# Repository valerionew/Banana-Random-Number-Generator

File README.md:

# Banana Random Number Generator

## Project description 
An Arduino based true random number generator. Takes it's peculiar name from the potassium-40 present in bananas, used as radiation source for the random number generatation.  
  
_Disclaimer: the radioactivity from the bananas doesn't quite make the difference, the background radiation is more than enough to make the generator work. Potassium is definitely detected, some tests conducted with pure KCl and KOH showed a huge increase in the detector activity._

1. [Project status](#project-status)  
1. [Hardware](#hardware)  
1. [Software](#software) 
1. [Enclosure](#enclosure) 

## Project status 
The current release is fully working. 
## Hardware 
The hardware is based around the popular ATMega328P and the STS-5 (a.k.a. CTC-5) Geiger-Müller tube.
## Software

As of this moment there are available two versions of the firmware:
- **minimal_test.c**: this version is fully compatible with the unmodified hardware. It uses the hardware interrupt INT0 and has proven to be unreliable when brought into an arduino environment due to interferences with the millis() function from the Wiring core. On it's own works with no problems. [Read more on this, in italian](https://www.valerionappi.it/chi-quadro/)
- **minimal_test_with capture.c**: this version and has proven to be much more reliable than the previous, since it captures the timer stamp via dedicated hardware and it's not subject to software delays. It's based on the timer capture function on PB0/ICP1 pin of the ATMega. This version needs a bodge wire between pin PD2 and pin PB0, as shown below:  

I'm currently working on an arduino version on the software, that will be published in this repo as soon as it gives consistent results.
In the future another version of the firmware which makes use of the hardware as a plain Geiger counter might be developed. Any help is welcome!
## Enclosure
The board is designed to fit in a laser cut acrylic enclosure to protect the user from the high voltage present onboard. 
The enclosure design files are included and licensed under [CC-BY-SA 4.0 license](http://creativecommons.org/licenses/by-sa/4.0/)

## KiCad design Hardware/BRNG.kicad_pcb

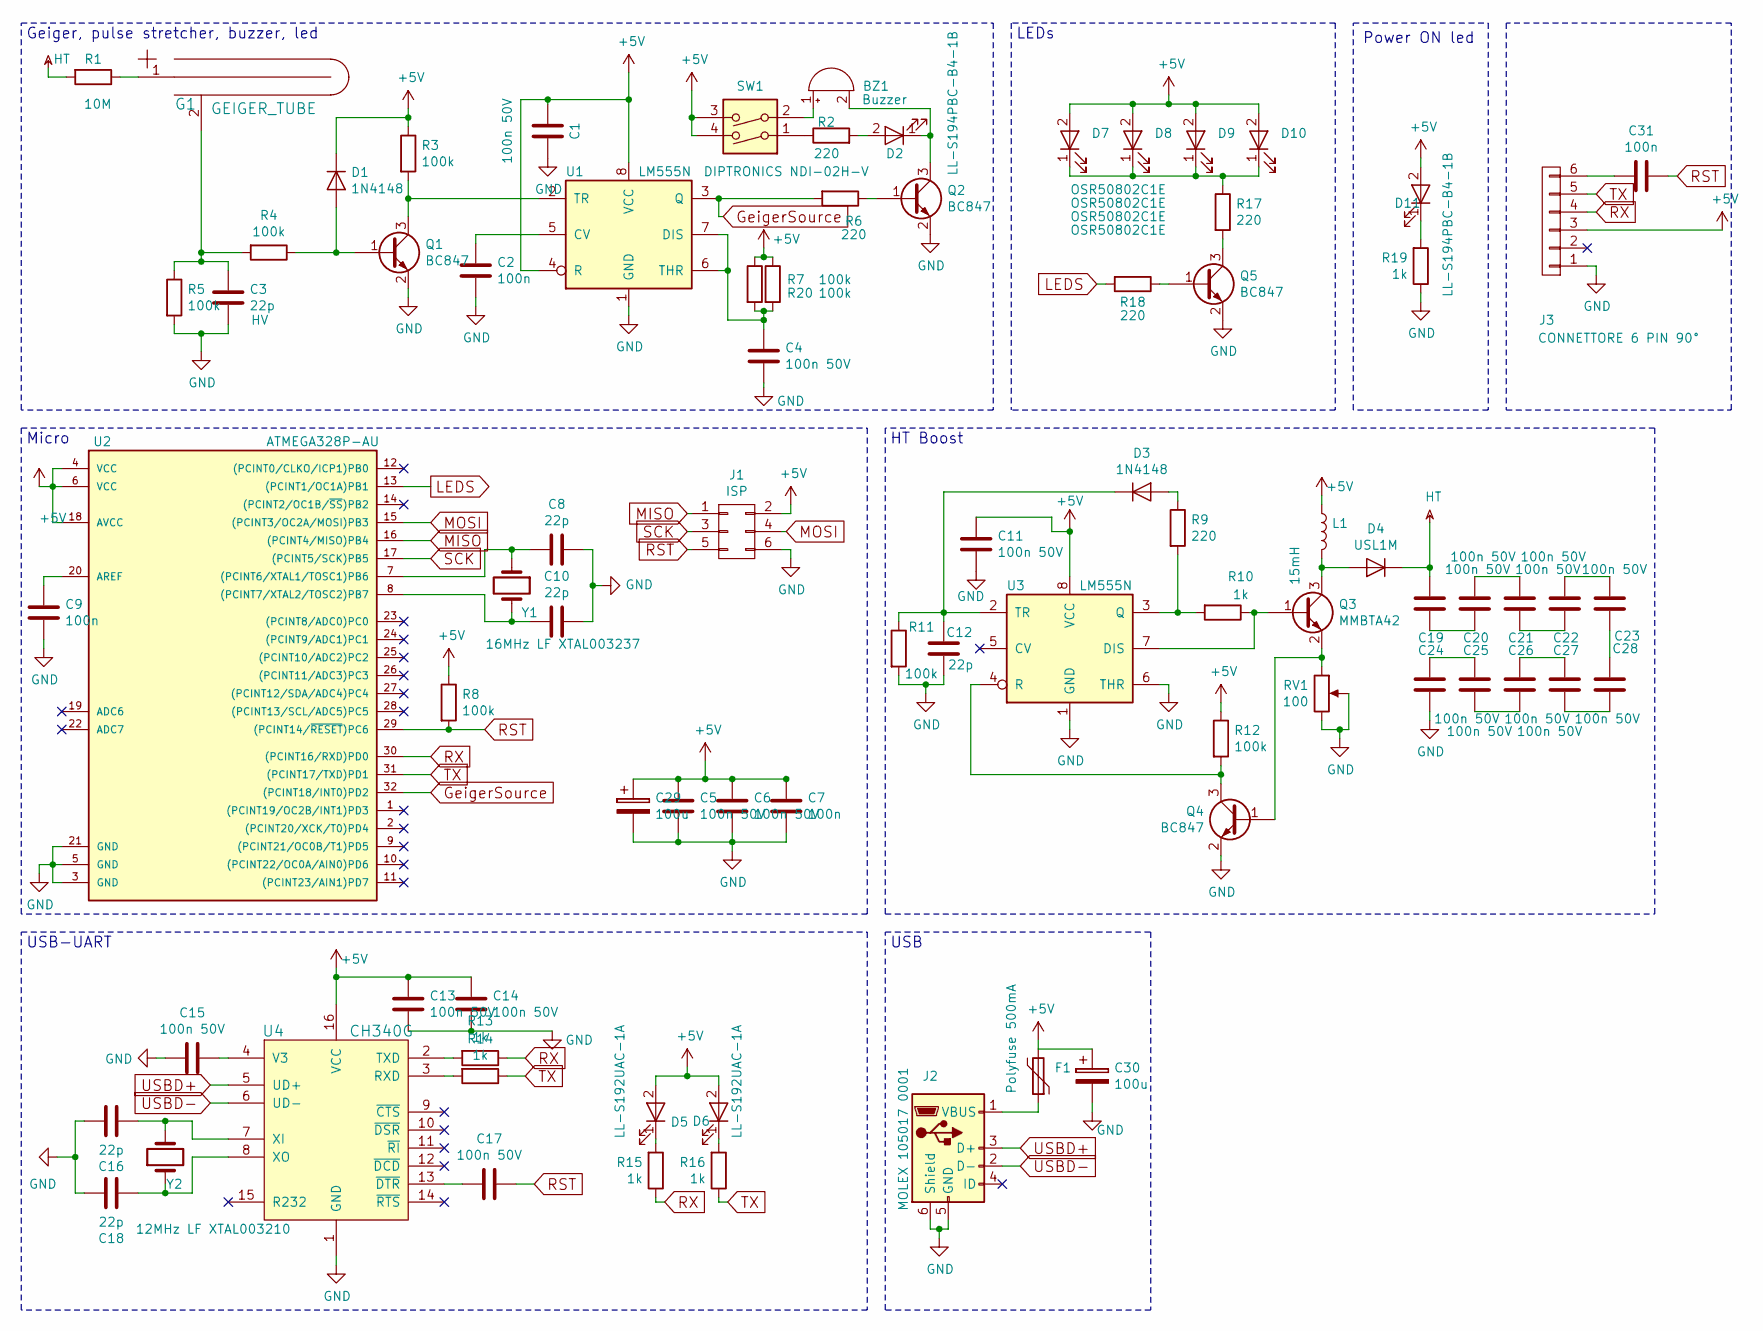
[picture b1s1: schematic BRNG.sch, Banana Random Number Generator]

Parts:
BZ1: Buzzer; Buzzer_12x9.5RM7.6
C1, C4, C5, C6, C11, C13, C14, C15, C17, C19, C20, C21, C22, C23, C24, C25, C26, C27, C28: 100n 50V; C_0805_HandSoldering
C2, C7, C9, C31: 100n; C_0805_HandSoldering
C3, C8, C10, C12, C16, C18: 22p; C_0805_HandSoldering
C29, C30: 100u; CP_Elec_6.3x5.3
D1, D3: 1N4148; D_SOD-123
D2, D11: LL-S194PBC-B4-1B; LED_0603_HandSoldering
D4: USL1M; D_SOD-123
D5, D6: LL-S192UAC-1A; LED_0603_HandSoldering
D7, D8, D9, D10: OSR50802C1E; 0802_side_led
F1: Polyfuse 500mA; R_1210_HandSoldering
G1: GEIGER_TUBE; Geiger
J1: ISP; Pin_Header_Straight_2x03_Pitch2.54mm
J2: MOLEX 105017 0001; USB_Micro-B_Molex-105017-0001
J3: CONNETTORE 6 PIN 90°; Pin_Header_Angled_1x06_Pitch2.54mm
L1: 15mH; L_Radial_D7.2mm_P3.00mm_MuRATA_1700
Q1, Q2, Q4, Q5: BC847; SOT-23_Handsoldering
Q3: MMBTA42; SOT-23_Handsoldering
R1: 10M; R_1206_HandSoldering
R2, R6, R9, R17, R18: 220; R_0805_HandSoldering
R3, R4, R5, R7, R8, R11, R12, R20: 100k; R_0805_HandSoldering
R10, R13, R14, R15, R16, R19: 1k; R_0805_HandSoldering
RV1: 100; Potentiometer_Trimmer_Vishay_T73XW_Vertical
SW1: DIPTRONICS NDI-02H-V; SW_DIP_x2_W7.62mm_Slide
U1, U3: LM555N; SOIC-8_3.9x4.9mm_Pitch1.27mm
U2: ATMEGA328P-AU; TQFP-32_7x7mm_Pitch0.8mm
U4: CH340G; SOP-16_4.4x10.4mm_Pitch1.27mm
Y1: 16MHz LF XTAL003237; Crystal_SMD_HC49-SD_HandSoldering
Y2: 12MHz LF XTAL003210; Crystal_SMD_HC49-SD_HandSoldering

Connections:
+5V: C1.2, C5.1, C6.1, C7.1, C11.1, C13.1, C14.1, C29.1, C30.1, D1.1 (K), D5.2 (A), D6.2 (A), D7.2 (A), D8.2 (A), D9.2 (A), D10.2 (A), D11.2 (A), F1.2, J1.2, J3.3, L1.1, R3.1, R7.1, R8.1, R12.1, R20.1, SW1.3, SW1.4, U1.4 (R), U1.8 (VCC), U2.4 (VCC), U2.6 (VCC), U2.18 (AVCC), U3.8 (VCC), U4.16 (VCC); also elsewhere on the board
GND: C1.1, C2.2, C3.2, C4.2, C5.2, C6.2, C7.2, C8.1, C9.2, C10.1, C11.2, C12.2, C13.2, C14.2, C15.2, C16.1, C18.1, C24.2, C29.2, C30.2, J1.6, J2.5 (GND), J2.6 (Shield), J3.1, Q1.2 (E), Q2.2 (E), Q4.2 (E), Q5.2 (E), R5.2, R11.2, R19.1, RV1.2, RV1.3, U1.1 (GND), U2.3 (GND), U2.5 (GND), U2.21 (GND), U3.1 (GND), U3.6 (THR), U4.1 (GND); also elsewhere on the board
GeigerSource: R6.2, U1.3 (Q), U2.32 ((PCINT18/INT0)PD2)
HT: C19.1, D4.1 (K), R1.2
LEDS: R18.2, U2.13 ((PCINT1/OC1A)PB1)
MISO: J1.1, U2.16 ((PCINT4/MISO)PB4); also elsewhere on the board
MOSI: J1.4, U2.15 ((PCINT3/OC2A/MOSI)PB3); also elsewhere on the board
unnamed: BZ1.1 (-), SW1.2
unnamed: BZ1.2 (+), D2.1 (K), Q2.3 (C)
unnamed: C2.1, U1.5 (CV)
unnamed: C3.1, G1.2, R4.2, R5.1
unnamed: C4.1, R7.2, R20.2, U1.6 (THR), U1.7 (DIS)
unnamed: C8.2, U2.7 ((PCINT6/XTAL1/TOSC1)PB6), Y1.1
unnamed: C9.1, U2.20 (AREF)
unnamed: C10.2, U2.8 ((PCINT7/XTAL2/TOSC2)PB7), Y1.2
unnamed: C12.1, D3.1 (K), R11.1, U3.2 (TR)
unnamed: C15.1, U4.4 (V3)
unnamed: C16.2, U4.7 (XI), Y2.2
unnamed: C17.2, U4.13 (~DTR)
unnamed: C18.2, U4.8 (XO), Y2.1
unnamed: C19.2, C20.2
unnamed: C20.1, C21.1
unnamed: C21.2, C22.2
unnamed: C22.1, C23.1
unnamed: C23.2, C28.1
unnamed: C24.1, C25.1
unnamed: C25.2, C26.2
unnamed: C26.1, C27.1
unnamed: C27.2, C28.2
unnamed: C31.1, J3.6
unnamed: D1.2 (A), Q1.1 (B), R4.1
unnamed: D2.2 (A), R2.2
unnamed: D3.2 (A), R9.1
unnamed: D4.2 (A), L1.2, Q3.3 (C)
unnamed: D5.1 (K), R15.2
unnamed: D6.1 (K), R16.2
unnamed: D7.1 (K), D8.1 (K), D9.1 (K), D10.1 (K), R17.1
unnamed: D11.1 (K), R19.2
unnamed: F1.1, J2.1 (VBUS)
unnamed: G1.1, R1.1
unnamed: Q1.3 (C), R3.2, U1.2 (TR)
unnamed: Q2.1 (B), R6.1
unnamed: Q3.1 (B), R10.1, U3.7 (DIS)
unnamed: Q3.2 (E), Q4.1 (B), RV1.1
unnamed: Q4.3 (C), R12.2, U3.4 (R)
unnamed: Q5.1 (B), R18.1
unnamed: Q5.3 (C), R17.2
unnamed: R2.1, SW1.1
unnamed: R9.2, R10.2, U3.3 (Q)
unnamed: R13.2, U4.2 (TXD)
unnamed: R14.2, U4.3 (RXD)
RST: C17.1, C31.2, J1.5, R8.2, U2.29 ((PCINT14/~RESET~)PC6); also elsewhere on the board
RX: J3.4, R13.1, R15.1, U2.30 ((PCINT16/RXD)PD0)
SCK: J1.3, U2.17 ((PCINT5/SCK)PB5); also elsewhere on the board
TX: J3.5, R14.1, R16.1, U2.31 ((PCINT17/TXD)PD1)
USBD+: J2.3 (D+), U4.5 (UD+)
USBD-: J2.2 (D-), U4.6 (UD-)

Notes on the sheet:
Micro
Geiger, pulse stretcher, buzzer, led
HT Boost
LEDs
Power ON led
USB-UART
USB

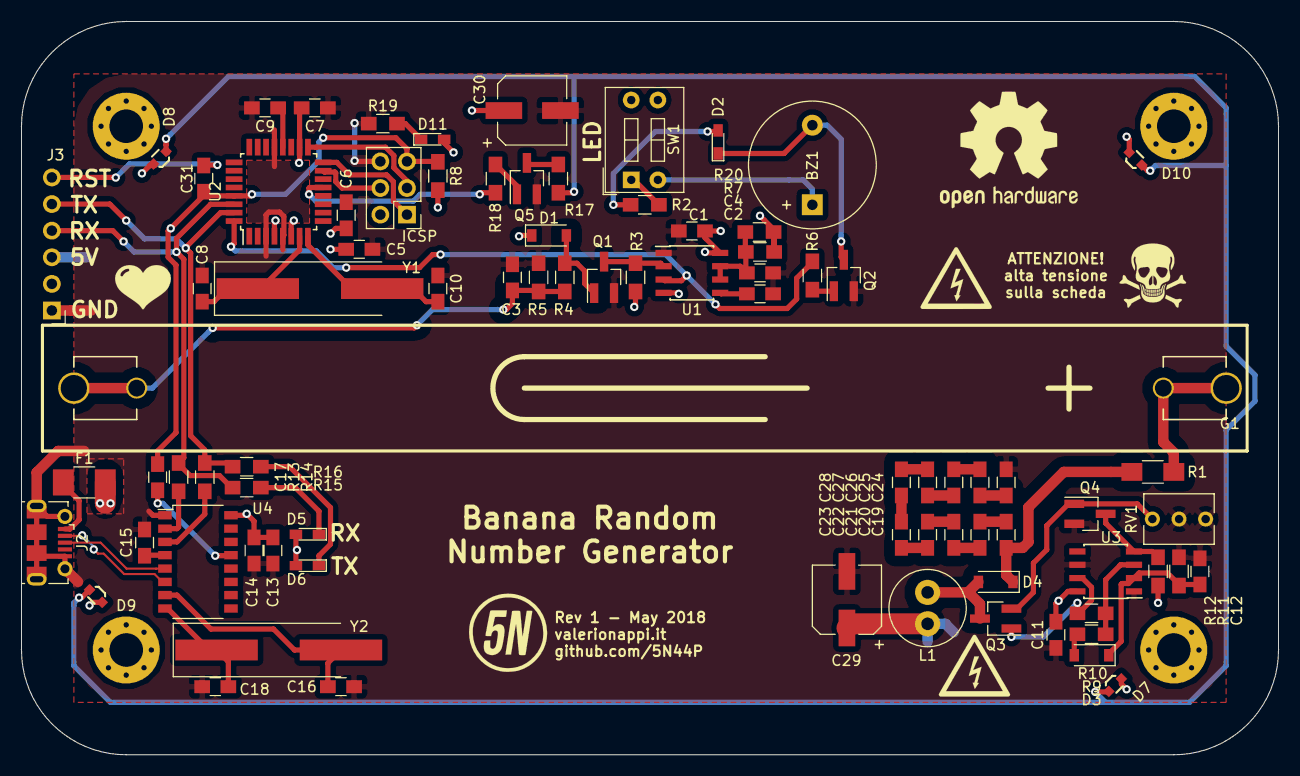
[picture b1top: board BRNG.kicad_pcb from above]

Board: 2 copper layers, 120.0 x 70.0 mm, 82 parts (0 on the bottom side), 57 nets.

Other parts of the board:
ICSP: ISP; Pin_Header_Straight_2x03_Pitch2.54mm

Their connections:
+5V: ICSP.2; also elsewhere on the board
GND: ICSP.6; also elsewhere on the board
MISO: ICSP.1; also elsewhere on the board
MOSI: ICSP.4; also elsewhere on the board
RST: ICSP.5; also elsewhere on the board
SCK: ICSP.3; also elsewhere on the board

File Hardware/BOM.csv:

Id;Ref;Package;Qty;Value
1;BZ1;Buzzer_12x9.5RM7.6;1;Buzzer
5;C11 C1 C4 C5 C6 C13 C14 C15 C17 C19 C20 C21 C22 C23 C24 C25 C26 C27 C28 C2 C7 C3 C9 C31;C_0805_HandSoldering;24;100n 50V
35;C29 C30;CP_Elec_6.3x5.3;2;100u 6V
11;C8 C10 C16 C18 C12;C_0805_HandSoldering;5;22p 10V
14;D2 D11;LED_0603_HandSoldering;2;LL-S194PBC-B4-1B
15;D1 D3 D4;D_SOD-123;3;USL1M
6;D5 D6;LED_0603_HandSoldering;2;LL-S192UAC-1A
37;D7 D8 D9 D10;0802_side_led;4;OSR50802C1E
16;F1;R_1210_HandSoldering;1;Polyfuse 500mA
17;G1;Geiger;1;STS-20 geiger + 2 KEYSTONE 3518P
18;ICSP;Pin_Header_Straight_2x03_Pitch2.54mm;1;ISP
19;J2;USB_Micro-B_Molex-105017-0001;1;MOLEX 105017 0001
4;J3;Pin_Header_Angled_1x06_Pitch2.54mm;1;Angled connector
20;L1;L_Radial_D7.2mm_P3.00mm_MuRATA_1700;1;15mH FASTRON 11PHC-153K-50
21;Q1 Q2 Q4 Q5;SOT-23_Handsoldering;4;BC847
22;Q3;SOT-23_Handsoldering;1;MMBTA42
23;R1;R_1206_HandSoldering;1;10M YAGEO RC1206JR-0710ML
7;R15 R16 R10 R13 R14 R19;R_0805_HandSoldering;6;1k
24;R2 R6 R9 R17 R18;R_0805_HandSoldering;5;220
26;R4 R5 R12 R11 R7 R20 R3 R8;R_0805_HandSoldering;8;100k
29;RV1;Potentiometer_Trimmer_Vishay_T73XW_Vertical;1;100
30;SW1;SW_DIP_x2_W7.62mm_Slide;1;DIPTRONICS NDI-02H-V
31;U1 U3;SOIC-8_3.9x4.9mm_Pitch1.27mm;2;LM555N
32;U2;TQFP-32_7x7mm_Pitch0.8mm;1;ATMEGA328P-AU
33;U4;SOP-16_4.4x10.4mm_Pitch1.27mm;1;CH340G
36;Y1;Crystal_SMD_HC49-SD_HandSoldering;1;16MHz LF XTAL003237
34;Y2;Crystal_SMD_HC49-SD_HandSoldering;1;12MHz LF XTAL003210

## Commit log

2018-03-14 First hardware release
2018-03-14 Create LICENSE
2018-03-22 minimal test
    Minimal test to try the quality of the random with minimal interference from interrupt.
2018-03-25 Small big bugfix
    fixed a bug that hanged the program once the buffer was filled the first time
2018-03-25 added led toggle for debug purposes
2018-03-28 removed led toggling
2018-03-29 Rename src/minimal_test_with_capture.c to src/capturetest/minimal_test_with_capture.c
2018-05-02 added license header
2018-05-02 added load script
2018-05-02 Fixes #5
2018-05-02 added enclosure license
2018-05-03 Rename src/test/minimal_test.c to src/minimal_test.c
2018-05-03 Rename src/capturetest/minimal_test_with_capture.c to src/minimal_test_with_capture.c
2018-05-03 Fixes #4
2018-05-03 added BOM
2018-05-03 changed BOM to use , instead of ;
2019-03-09 Added the pi computation GUI code for processing
    With this program you can see pi being calculated with the monte carlo method, using the random numbers from the generator as inputs
2019-09-09 added control for onboard LEDs
2019-09-09 added info on the avrdude conf

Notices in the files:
Hardware/BRNG.kicad_pcb:
Hardware released under CC-BY-SA 4.0 license
Hardware/BRNG.sch:
https://creativecommons.org/licenses/by-sa/4.0
README.md:
License: CC BY-SA 4.0
License: GPL v3
